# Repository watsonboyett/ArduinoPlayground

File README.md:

# ArduinoPlayground
A collection of simple Arduino programs that perform various tasks (mostly for costumes and other one-off stuff).

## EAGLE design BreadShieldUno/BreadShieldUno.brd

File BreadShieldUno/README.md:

BreadShieldUno
==============

A proper breadboard shield for the Arduino Uno Rev3

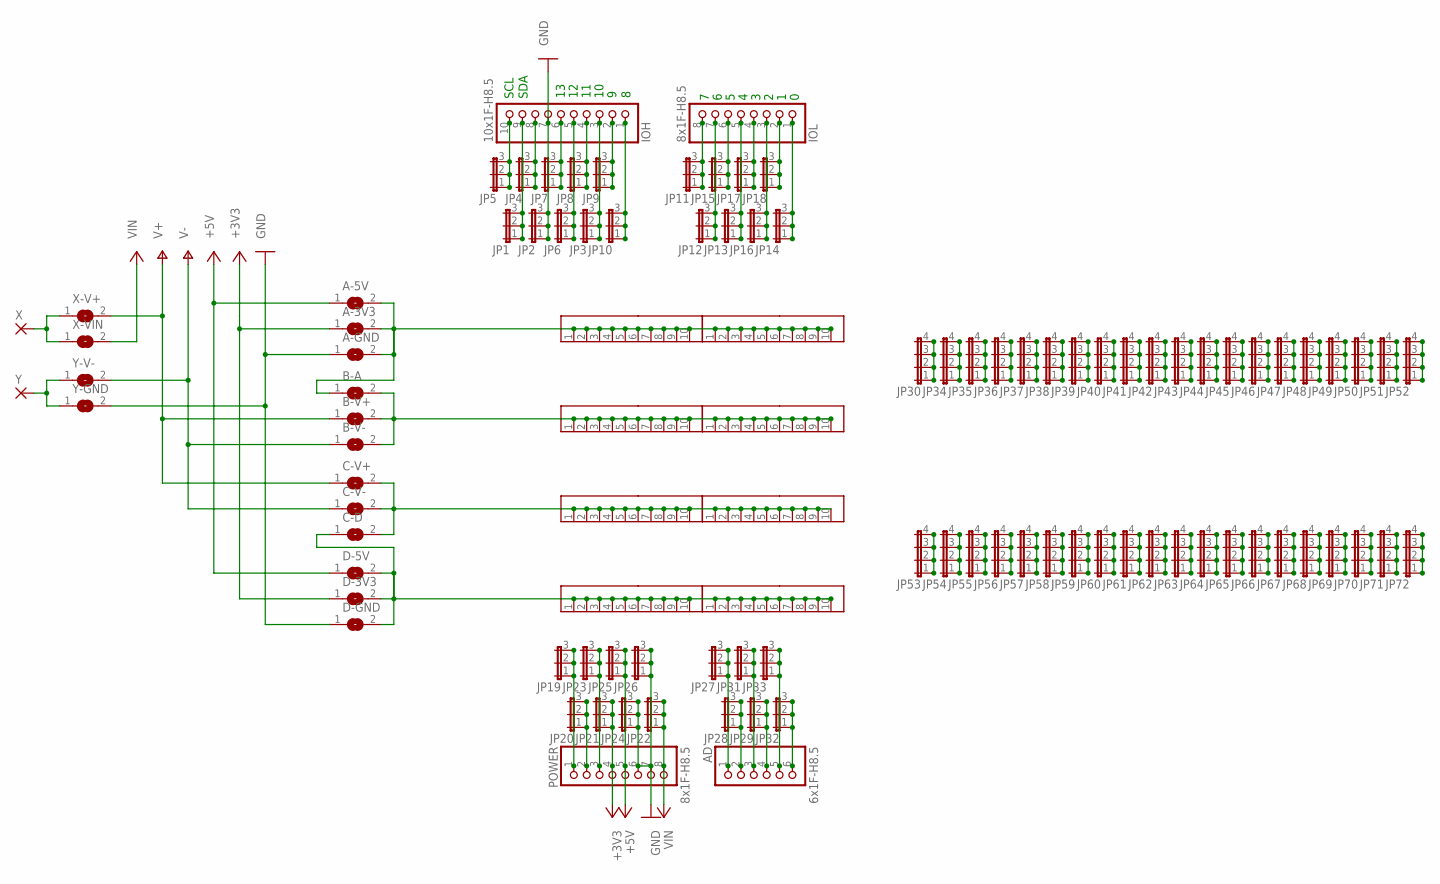
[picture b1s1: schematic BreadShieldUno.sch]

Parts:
A, A2: JP10B; JP10-1
A-3V3, A-5V: SJ
A-GND: SJ
AD: 6x1F-H8.5; 1X06
B, B2: JP10B; JP10-1
B-A: SJ
B-V+: SJ
B-V-: SJ
C, C2: JP10B; JP10-1
C-D: SJ
C-V+: SJ
C-V-: SJ
D, D2: JP10B; JP10-1
D-3V3, D-5V: SJ
D-GND: SJ
IOH: 10x1F-H8.5; 1X10
IOL: 8x1F-H8.5; 1X08
JP1, JP2, JP3, JP4, JP5, JP6, JP7, JP8, JP9, JP10, JP11, JP12, JP13, JP14, JP15, JP16, JP17, JP18, JP19, JP20, JP21, JP22, JP23, JP24, JP25, JP26, JP27, JP28, JP29, JP31, JP32, JP33: JP2E; JP2
JP30, JP34, JP35, JP36, JP37, JP38, JP39, JP40, JP41, JP42, JP43, JP44, JP45, JP46, JP47, JP48, JP49, JP50, JP51, JP52, JP53, JP54, JP55, JP56, JP57, JP58, JP59, JP60, JP61, JP62, JP63, JP64, JP65, JP66, JP67, JP68, JP69, JP70, JP71, JP72: JP4E; JP4
POWER: 8x1F-H8.5; 1X08
X: 3,81/1,4
X-V+: SJ
X-VIN: SJ
Y: 3,81/1,4
Y-GND: SJ
Y-V-: SJ

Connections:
+3V3: A-3V3.1, D-3V3.1, JP21.1, JP21.2, JP21.3, POWER.4
+5V: A-5V.1, D-5V.1, JP25.1, JP25.2, JP25.3, POWER.5
GND: A-GND.1, D-GND.1, IOH.7, JP2.1, JP2.2, JP2.3, JP24.1, JP24.2, JP24.3, JP26.1, JP26.2, JP26.3, POWER.6, POWER.7, Y-GND.2
GND1: IOL.5, JP13.1, JP13.2, JP13.3
GND2: AD.4, JP29.1, JP29.2, JP29.3
unnamed: A.1, A.2, A.3, A.4, A.5, A.6, A.7, A.8, A.9, A.10, A2.1, A2.2, A2.3, A2.4, A2.5, A2.6, A2.7, A2.8, A2.9, A2.10, A-3V3.2, A-5V.2, A-GND.2, B-A.1
unnamed: B.1, B.2, B.3, B.4, B.5, B.6, B.7, B.8, B.9, B.10, B2.1, B2.2, B2.3, B2.4, B2.5, B2.6, B2.7, B2.8, B2.9, B2.10, B-A.2, B-V+.2, B-V-.2
unnamed: C.1, C.2, C.3, C.4, C.5, C.6, C.7, C.8, C.9, C.10, C2.1, C2.2, C2.3, C2.4, C2.5, C2.6, C2.7, C2.8, C2.9, C2.10, C-D.2, C-V+.2, C-V-.2
unnamed: C-D.1, D.1, D.2, D.3, D.4, D.5, D.6, D.7, D.8, D.9, D.10, D2.1, D2.2, D2.3, D2.4, D2.5, D2.6, D2.7, D2.8, D2.9, D2.10, D-3V3.2, D-5V.2, D-GND.2
unnamed: X.1, X-V+.1, X-VIN.1
unnamed: Y.1, Y-GND.1, Y-V-.1
unnamed: IOH.10, JP5.1, JP5.2, JP5.3
unnamed: IOH.9, JP1.1, JP1.2, JP1.3
unnamed: IOH.8, JP4.1, JP4.2, JP4.3
unnamed: IOH.6, JP7.1, JP7.2, JP7.3
unnamed: IOH.5, JP6.1, JP6.2, JP6.3
unnamed: IOH.4, JP8.1, JP8.2, JP8.3
unnamed: IOH.3, JP3.1, JP3.2, JP3.3
unnamed: IOH.2, JP9.1, JP9.2, JP9.3
unnamed: IOH.1, JP10.1, JP10.2, JP10.3
unnamed: IOL.8, JP11.1, JP11.2, JP11.3
unnamed: IOL.7, JP12.1, JP12.2, JP12.3
unnamed: IOL.6, JP15.1, JP15.2, JP15.3
unnamed: IOL.4, JP17.1, JP17.2, JP17.3
unnamed: IOL.3, JP16.1, JP16.2, JP16.3
unnamed: IOL.2, JP18.1, JP18.2, JP18.3
unnamed: IOL.1, JP14.1, JP14.2, JP14.3
unnamed: JP19.1, JP19.2, JP19.3, POWER.1
unnamed: JP20.1, JP20.2, JP20.3, POWER.2
unnamed: JP23.1, JP23.2, JP23.3, POWER.3
unnamed: AD.1, JP27.1, JP27.2, JP27.3
unnamed: AD.2, JP28.1, JP28.2, JP28.3
unnamed: AD.3, JP31.1, JP31.2, JP31.3
unnamed: AD.5, JP33.1, JP33.2, JP33.3
unnamed: AD.6, JP32.1, JP32.2, JP32.3
unnamed: JP30.1, JP30.2, JP30.3, JP30.4
unnamed: JP34.1, JP34.2, JP34.3, JP34.4
unnamed: JP35.1, JP35.2, JP35.3, JP35.4
unnamed: JP36.1, JP36.2, JP36.3, JP36.4
unnamed: JP37.1, JP37.2, JP37.3, JP37.4
unnamed: JP38.1, JP38.2, JP38.3, JP38.4
unnamed: JP39.1, JP39.2, JP39.3, JP39.4
unnamed: JP40.1, JP40.2, JP40.3, JP40.4
unnamed: JP41.1, JP41.2, JP41.3, JP41.4
unnamed: JP42.1, JP42.2, JP42.3, JP42.4
unnamed: JP43.1, JP43.2, JP43.3, JP43.4
unnamed: JP44.1, JP44.2, JP44.3, JP44.4
unnamed: JP45.1, JP45.2, JP45.3, JP45.4
unnamed: JP46.1, JP46.2, JP46.3, JP46.4
unnamed: JP47.1, JP47.2, JP47.3, JP47.4
unnamed: JP48.1, JP48.2, JP48.3, JP48.4
unnamed: JP49.1, JP49.2, JP49.3, JP49.4
unnamed: JP50.1, JP50.2, JP50.3, JP50.4
unnamed: JP51.1, JP51.2, JP51.3, JP51.4
unnamed: JP52.1, JP52.2, JP52.3, JP52.4
unnamed: JP53.1, JP53.2, JP53.3, JP53.4
unnamed: JP54.1, JP54.2, JP54.3, JP54.4
unnamed: JP55.1, JP55.2, JP55.3, JP55.4
unnamed: JP56.1, JP56.2, JP56.3, JP56.4
unnamed: JP57.1, JP57.2, JP57.3, JP57.4
unnamed: JP58.1, JP58.2, JP58.3, JP58.4
unnamed: JP59.1, JP59.2, JP59.3, JP59.4
unnamed: JP60.1, JP60.2, JP60.3, JP60.4
unnamed: JP61.1, JP61.2, JP61.3, JP61.4
unnamed: JP62.1, JP62.2, JP62.3, JP62.4
unnamed: JP63.1, JP63.2, JP63.3, JP63.4
unnamed: JP64.1, JP64.2, JP64.3, JP64.4
unnamed: JP65.1, JP65.2, JP65.3, JP65.4
unnamed: JP66.1, JP66.2, JP66.3, JP66.4
unnamed: JP67.1, JP67.2, JP67.3, JP67.4
unnamed: JP68.1, JP68.2, JP68.3, JP68.4
unnamed: JP69.1, JP69.2, JP69.3, JP69.4
unnamed: JP70.1, JP70.2, JP70.3, JP70.4
unnamed: JP71.1, JP71.2, JP71.3, JP71.4
unnamed: JP72.1, JP72.2, JP72.3, JP72.4
V+: B-V+.1, C-V+.1, X-V+.2
V-: B-V-.1, C-V-.1, Y-V-.2
VIN: JP22.1, JP22.2, JP22.3, POWER.8, X-VIN.2

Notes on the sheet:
SDA
SCL

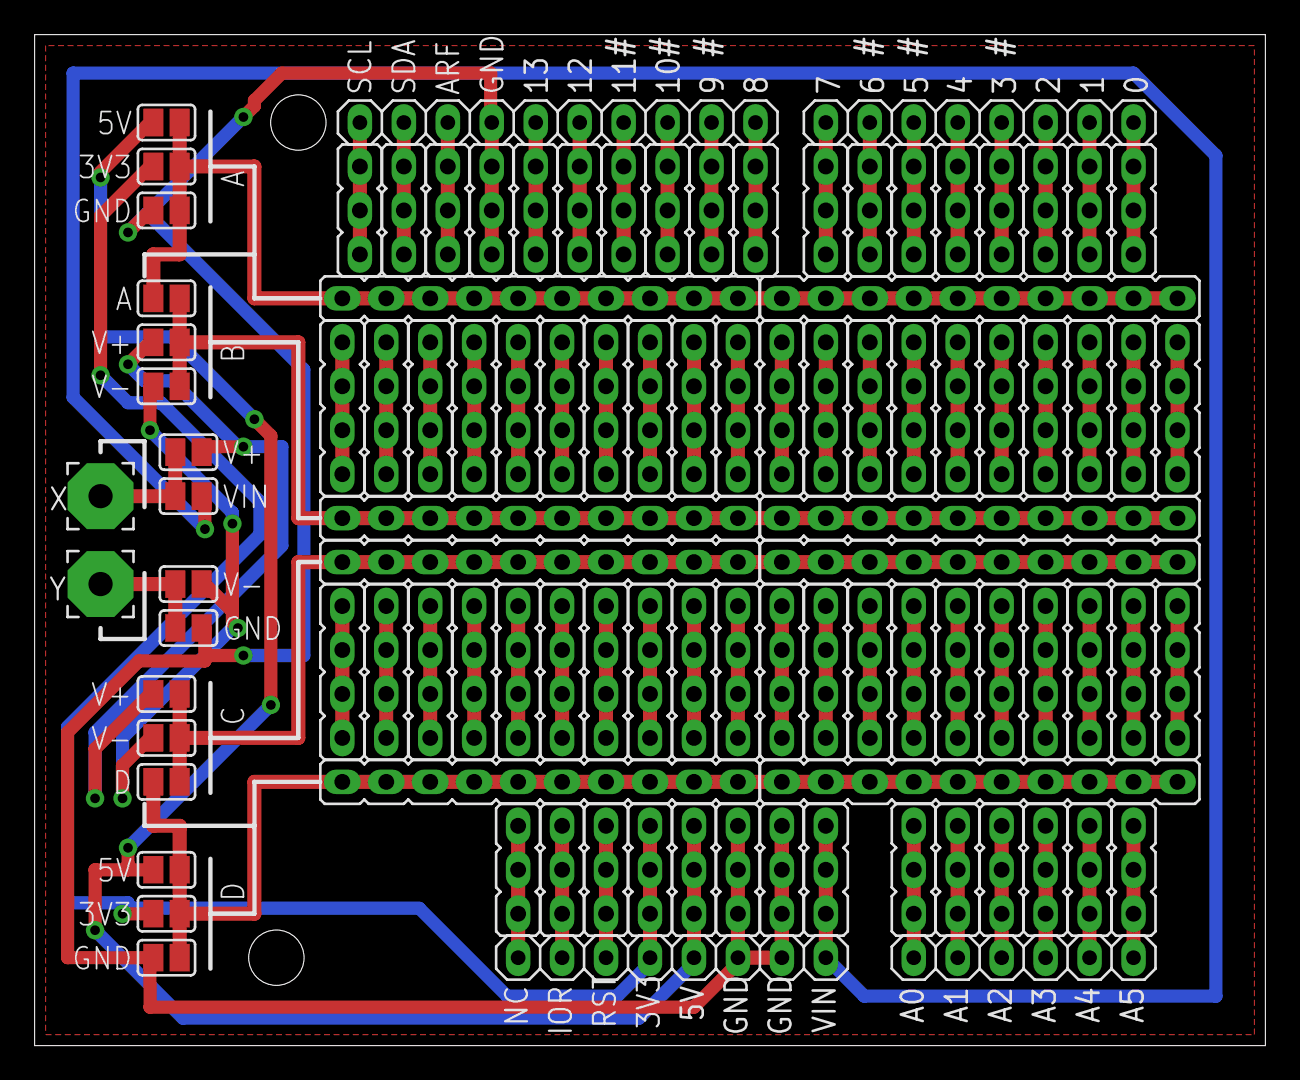
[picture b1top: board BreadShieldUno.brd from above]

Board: 2 copper layers, 71.1 x 58.4 mm, 102 parts (0 on the bottom side), 78 nets.

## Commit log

2016-01-01 Consolidated several smaller projects into this repo for easier management.
2016-01-21 Total revamp: now using circular buffers to generate new colors as existing ones vanish.
2017-06-08 Updated timing values
2017-11-11 Added code for smoothly fading strips of NeoPixels
2017-11-11 Added LED intensity lenearization script (in python) and output header files (in C)
